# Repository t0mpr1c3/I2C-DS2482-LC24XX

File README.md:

I2C-DS2482-24LCxx
=================

Dual purpose, daisy chainable breakout board for DS2482-100 OneWire master or 24LCxx EEPROM.

Released under the [Creative Commons License Attribution-ShareAlike 3.0](http://creativecommons.org/licenses/by-sa/3.0/)

Version history
---------------

_IW01_

First version.

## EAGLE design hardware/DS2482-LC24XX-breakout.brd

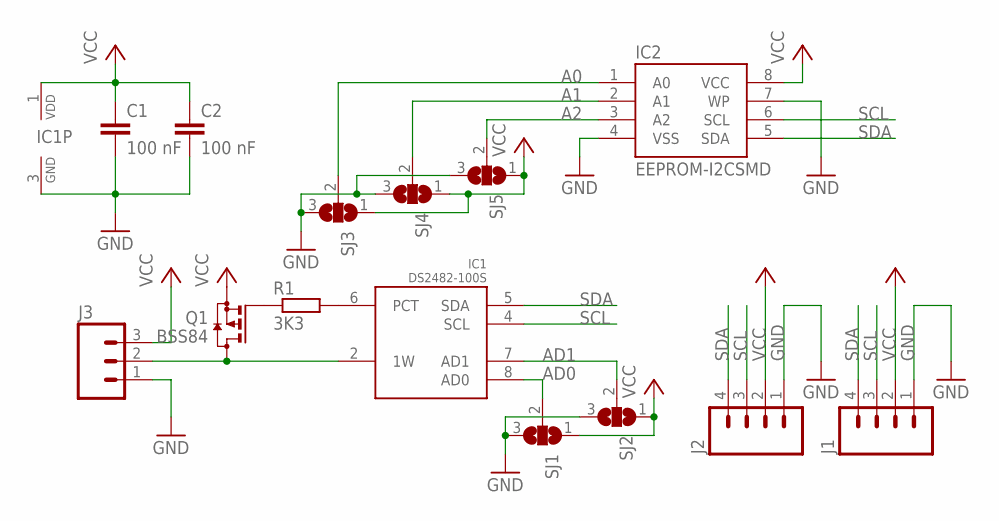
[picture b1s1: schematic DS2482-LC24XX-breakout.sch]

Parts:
C1, C2: 100 nF; C0603
IC1: DS2482-100S; SO08
IC2: EEPROM-I2CSMD; SO08
J1, J2: M04PTH; 1X04
J3: M03PTH; 1X03
Q1: BSS84; SOT23
R1: 3K3; R0805
SJ1, SJ2, SJ3, SJ4, SJ5: SJ2W; SJ_2

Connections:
A0: IC2.1 (A0), SJ3.2
A1: IC2.2 (A1), SJ4.2
A2: IC2.3 (A2), SJ5.2
AD0: IC1.8 (AD0), SJ1.2
AD1: IC1.7 (AD1), SJ2.2
GND: C1.2, C2.2, IC1.3 (GND), IC2.4 (VSS), IC2.7 (WP), J1.1, J2.1, J3.1, SJ1.3, SJ2.3, SJ3.3, SJ4.3, SJ5.3
unnamed: IC1.2 (1W), J3.2, Q1.3 (D)
unnamed: IC1.6 (PCT), R1.2
unnamed: Q1.1 (G), R1.1
SCL: IC1.4 (SCL), IC2.6 (SCL), J1.3, J2.3
SDA: IC1.5 (SDA), IC2.5 (SDA), J1.4, J2.4
VCC: C1.1, C2.1, IC1.1 (VDD), IC2.8 (VCC), J1.2, J2.2, J3.3, Q1.2 (S), SJ1.1, SJ2.1, SJ3.1, SJ4.1, SJ5.1

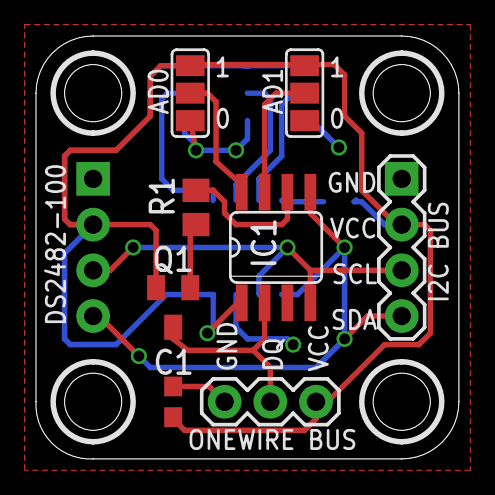
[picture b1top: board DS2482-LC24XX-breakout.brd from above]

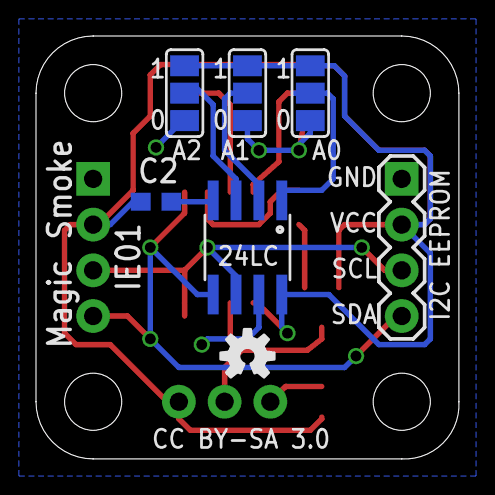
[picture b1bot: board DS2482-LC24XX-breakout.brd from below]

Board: 4 copper layers, 23.5 x 23.5 mm, 15 parts (7 on the bottom side), 12 nets.

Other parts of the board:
U$3: OSHW-LOGO-S

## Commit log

2013-11-18 gerbers
2013-11-20 stop mask over vias
2013-11-26 tweak gerbers
2013-12-03 IW01 for Seeedstudio
2013-12-24 IW01 Elecrow order

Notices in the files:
hardware/DS2482-LC24XX-breakout.brd:
CC BY-SA 3.0
parts and their libraries:
SparkFun: Licensing: CC v3.0 Share-Alike You are welcome to use this library for commercial purposes.
